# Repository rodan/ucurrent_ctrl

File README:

an overkill MSP430F5510 based project that controls the power delivery to Dave's uCurrent.

if you forget to turn off the uCurrent you will find the enclosed 2032 Li cell completely flat the next day.
this project provides a timeout feature to the uCurrent. a push-button is used to start up both this circuit and the uCurrent.
multiple presses will either reset the timeout counter or increase the timeout period.
the initial timeout period can be optionally modified via a 3V serial uart.
also in case the output voltage is low enough for a given period the uCurrent is turned off.

uC pinout:
 - P1.1  IN  digital - push button trigger
 - P1.4  OUT digital - power-latch my circuit
 - P1.5  OUT digital - enable power delivery to the uCurrent
 - P2.0  OUT digital - blinky
 - P6.0  IN  analog  - battery voltage
 - P4.1  IO          - SDA (i2c for ADS1110)
 - P4.2  IO          - SCL

connectors:
 - external power - either 3V Li Cell or 3.7V LiPo/Li-ion (MOLEX 0530470210)
 - push button    - optional external push button tied to the case (MOLEX 0530470210)
 - ucurrent power - uCurrent connections (MOLEX 0530470210)
 - debug          - TI spy-bi-wire interface and serial uart for programming, debug and user input (MOLEX 0530470610)

power:
 - the uCurrent has the cell unpopulated and the power switch set to the "ON" position.
 - this circuit will provide the 3V needed to the uCurent

 homepage:        https://github.com/rodan/ucurrent_ctrl
 author:          Petre Rodan <2b4eda@subdimension.ro>
 license:         GNU GPLv3

 images of the prototype are available here: 
 https://photos.app.goo.gl/GjHpzLgLqz9fdpvY7

 parts of the code were originally forked from the openchronos-ng project [1]. 
 handling of settings based on code from Graham Fountain.

 software requirements:

   msp430 toolchain

[1] http://openchronos-ng.sourceforge.net

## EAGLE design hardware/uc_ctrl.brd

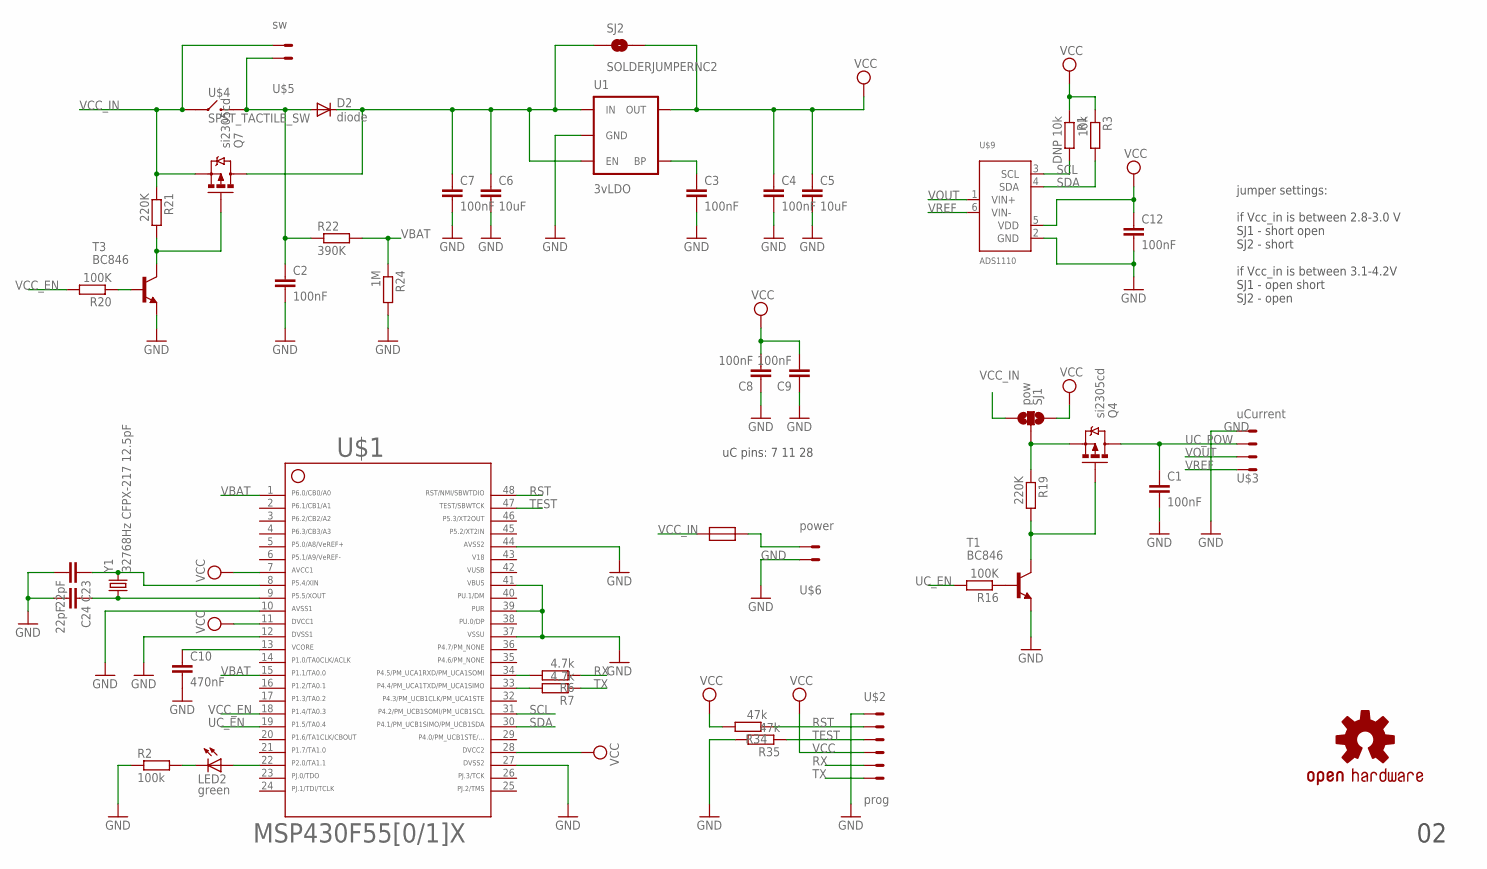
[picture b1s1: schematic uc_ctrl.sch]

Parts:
C1, C2, C3, C4, C7, C8, C9, C12: 100nF; C0805
C5, C6: 10uF; C0805
C10: 470nF; C0805
C23, C24: 22pF; C0805
D2: diode; SMA-DIODE
LED2: green; CHIPLED_0805
Q4, Q7: si2305cd; SOT23-3_POWER
R1: DNP 10k; R0805W
R2: 100k; R0805W
R3: 10k; R0805W
R6, R7: 4.7k; R0805W
R16, R20: 100K; R0805W
R19, R21: 220K; R0805W
R22: 390K; R0805W
R24: 1M; R0805W
R34, R35: 47k; R0805W
SJ1: pow; SJ_3_PASTE1&2
SJ2: SOLDERJUMPERNC2; SJ_2S-NOTRACE
T1, T3: BC846; SOT23
U1: 3vLDO; SOT23-5
U$1: F55[0/1]X---PT48; PT48
U$2: prog; 0530480610
U$3: uCurrent; 0530480401
U$4: SPST_TACTILE_SW; 6X3.5_TACTILE_SW
U$5: sw; 0530480210
U$6: power; 0530480210
U$7: OSHW-LOGOM; OSHW-LOGO-M
U$8: RESETTABLE; 1210
U$9: ADS1110; SOT23-6
Y1: 32768Hz CFPX-217 12.5pF; CRYSTAL-SMD-3.2X1.5

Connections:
42: U$1.42
43: U$1.43
46: U$1.46
GND: C1.2, C2.2, C3.2, C4.2, C5.2, C6.2, C7.2, C8.1, C9.1, C10.2, C12.2, C23.2, C24.2, R2.1, R24.2, R35.2, T1.2 (E), T3.2 (E), U1.2 (GND), U$1.10, U$1.12, U$1.27, U$1.37, U$1.39, U$1.41, U$1.44, U$2.1, U$3.1, U$6.P$1 (1), U$9.2 (GND)
unnamed: LED2.C, R2.2
unnamed: LED2.A, U$1.22
unnamed: R16.1, T1.1 (B)
unnamed: C6.1, C7.1, D2.C, Q7.3 (D), SJ2.1, U1.1 (IN), U1.3 (EN)
unnamed: C3.1, U1.4 (BP)
unnamed: C10.1, U$1.13
unnamed: Q4.2 (S), R19.1, SJ1.2
unnamed: U$6.P$2 (2), U$8.P$2
unnamed: R6.2, U$1.34
unnamed: R7.2, U$1.33
unnamed: C24.1, U$1.9, Y1.P$1 (1)
unnamed: C23.1, U$1.8, Y1.P$2 (2)
unnamed: Q4.1 (G), R19.2, T1.3 (C)
unnamed: R20.1, T3.1 (B)
unnamed: Q7.1 (G), R21.2, T3.3 (C)
PUSH: C2.1, D2.A, R22.1, U$4.2, U$5.P$1 (1)
RST: R34.1, U$1.48, U$2.2
RX: R6.1, U$2.5
SCL: R1.2, U$1.31, U$9.3 (SCL)
SDA: R3.2, U$1.30, U$9.4 (SDA)
TEST: R35.1, U$1.47, U$2.3
TX: R7.1, U$2.6
UC_EN: R16.2, U$1.19
UC_POW: C1.1, Q4.3 (D), U$3.2
VBAT: R22.2, R24.1, U$1.1, U$1.15
VCC: C4.1, C5.1, C8.2, C9.2, C12.1, R1.1, R3.1, R34.2, SJ1.1, SJ2.2, U1.5 (OUT), U$1.7, U$1.11, U$1.28, U$2.4, U$9.5 (VDD)
VCC_EN: R20.2, U$1.18
VCC_IN: Q7.2 (S), R21.1, SJ1.3, U$4.1, U$5.P$2 (2), U$8.P$1
VOUT: U$3.3, U$9.1 (VIN+)
VREF: U$3.4, U$9.6 (VIN-)

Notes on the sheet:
uC pins: 7 11 28
jumper settings: if Vcc_in is between 2.8-3.0 V SJ1 - short open SJ2 - short if Vcc_in is between 3.1-4.2V SJ1 - open short SJ2 - open

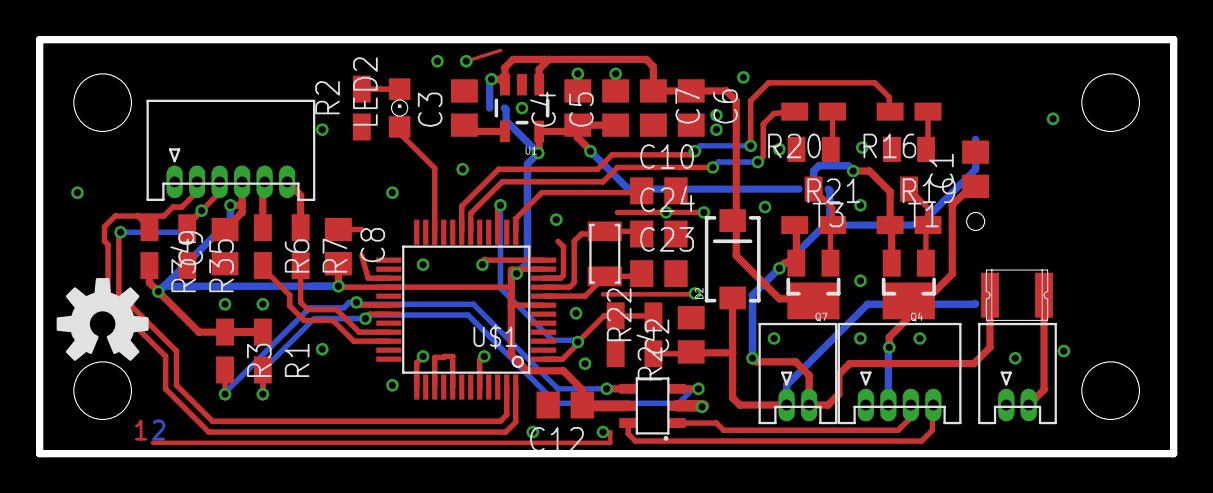
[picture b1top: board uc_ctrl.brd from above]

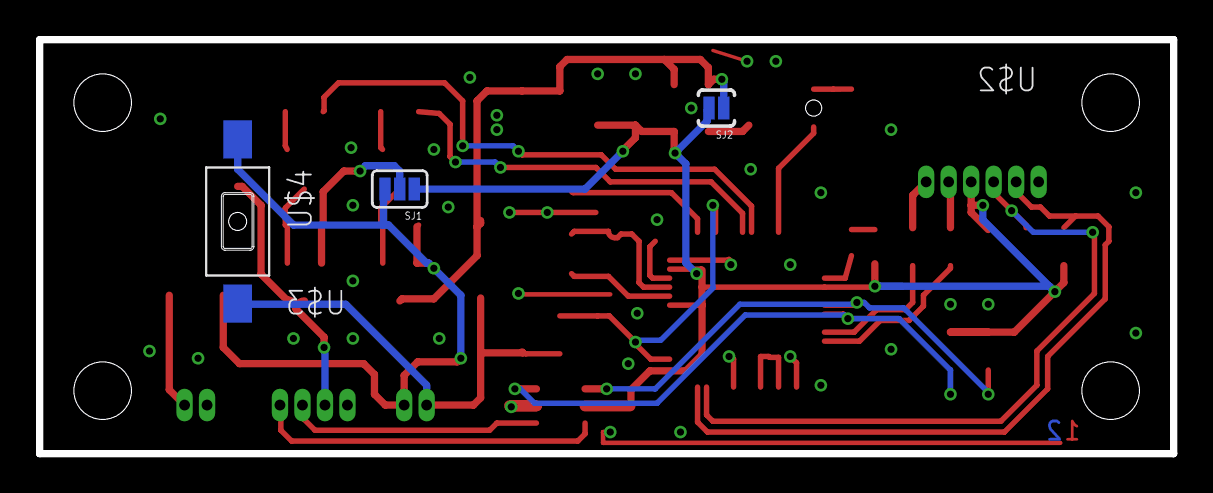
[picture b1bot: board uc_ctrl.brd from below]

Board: 2 copper layers, 63.0 x 23.0 mm, 45 parts (3 on the bottom side), 31 nets.

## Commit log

2013-12-27 add pcb
2013-12-27 also read uCurrent output voltage
2013-12-28 rev 2
2013-12-28 cleanup
2013-12-29 add 16bit adc
2013-12-29 sent gerbers to manufacturer
2013-12-29 add 0.5mm to board width
2014-01-25 add support for ADS1110
2014-01-26 add flash r/w driver
2014-01-26 add uart UI
2014-01-27 remove python scripts
2014-01-27 add rel delta capability to eadc
2014-05-12 unused pin tweaks
2015-08-27 trigger conversion only if setting is enabled
2018-09-01 email change
2018-12-13 change img location
2019-01-06 update compiler, remove pragma vector
2019-01-12 add suport for CCS
    add suport for CCS
2019-01-12 fix CSS warnings
2019-01-12 add ifdefs
2019-01-12 add hardware i2c
2019-01-12 cleanup timer_a0
2019-01-12 adc update
2019-01-12 working
2019-01-12 i2c cleanup
2019-01-13 update str_to_uint16()
2019-01-13 fix 2 ULP warnings
2019-01-13 dont blink no led
2021-12-08 makefile update
2021-12-08 compatibility with gcc 9.3
2021-12-10 rev3 redesign - skeleton stage
2021-12-10 stage 2 project migration
2021-12-11 rewrite readme
2021-12-13 scheduling works
2021-12-13 adc read conflicts with uart rx
2021-12-14 uart needs LPM1 due to dependency on SMCLK
2022-01-09 changes needed by latest HAL lib
2022-01-12 uart interface changes needed by latest atlas430

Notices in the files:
parts and their libraries:
SparkFun-DiscreteSemi: Licensing: CC v3.0 Share-Alike You are welcome to use this library for commercial purposes.
